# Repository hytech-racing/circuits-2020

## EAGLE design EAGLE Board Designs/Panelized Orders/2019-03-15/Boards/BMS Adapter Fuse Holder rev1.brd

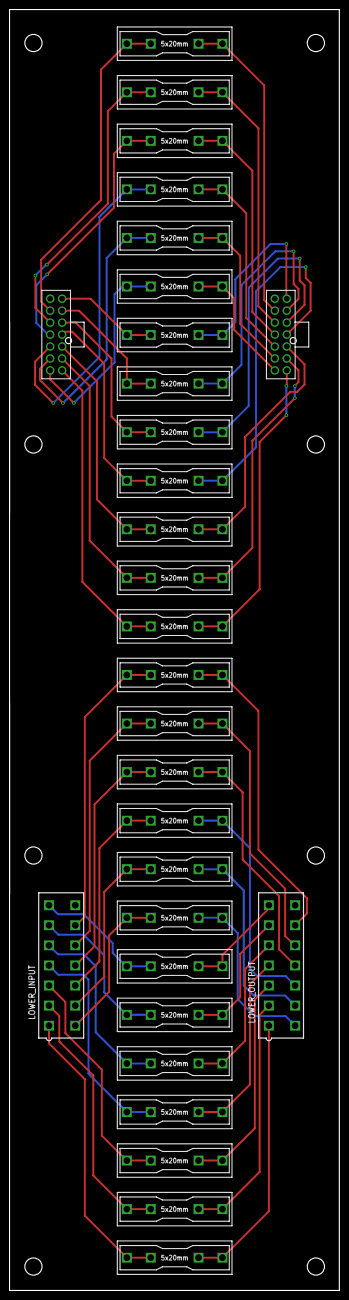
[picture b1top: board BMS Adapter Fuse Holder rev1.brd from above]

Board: 2 copper layers, 69.0 x 268.0 mm, 30 parts (0 on the bottom side), 52 nets.

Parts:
LOWER_INPUT: CONNECTOR-14; MINIFIT_5566-14
LOWER_OUTPUT: CONNECTOR-14; MINIFIT_5566-14
U$1, U$2, U$3, U$4, U$5, U$6, U$7, U$8, U$9, U$10, U$11, U$12, U$13, U$14, U$15, U$16, U$17, U$18, U$19, U$20, U$21, U$22, U$23, U$24, U$25, U$26: 1A; 0751.0110
UPPER_INPUT: CONNECTOR-14NANO-FIT_VERTICAL-14; NANO-FIT_VERTICAL-14
UPPER_OUTPUT: CONNECTOR-14NANO-FIT_VERTICAL-14; NANO-FIT_VERTICAL-14

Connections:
unnamed: LOWER_OUTPUT.1, U$1.L1, U$1.L2
unnamed: LOWER_OUTPUT.2, U$2.L1, U$2.L2
unnamed: LOWER_OUTPUT.3, U$3.L1, U$3.L2
unnamed: LOWER_OUTPUT.4, U$4.L1, U$4.L2
unnamed: LOWER_OUTPUT.5, U$5.L1, U$5.L2
unnamed: LOWER_OUTPUT.6, U$6.L1, U$6.L2
unnamed: LOWER_OUTPUT.7, U$7.L1, U$7.L2
unnamed: LOWER_OUTPUT.8, U$8.L1, U$8.L2
unnamed: LOWER_OUTPUT.9, U$9.L1, U$9.L2
unnamed: LOWER_OUTPUT.10, U$10.L1, U$10.L2
unnamed: LOWER_OUTPUT.11, U$11.L1, U$11.L2
unnamed: LOWER_OUTPUT.12, U$12.L1, U$12.L2
unnamed: LOWER_OUTPUT.13, U$13.L1, U$13.L2
unnamed: U$14.L1, U$14.L2, UPPER_OUTPUT.P$1
unnamed: U$15.L1, U$15.L2, UPPER_OUTPUT.P$2
unnamed: U$16.L1, U$16.L2, UPPER_OUTPUT.P$3
unnamed: U$17.L1, U$17.L2, UPPER_OUTPUT.P$4
unnamed: U$18.L1, U$18.L2, UPPER_OUTPUT.P$5
unnamed: U$19.L1, U$19.L2, UPPER_OUTPUT.P$6
unnamed: U$20.L1, U$20.L2, UPPER_OUTPUT.P$7
unnamed: U$21.L1, U$21.L2, UPPER_OUTPUT.P$8
unnamed: U$22.L1, U$22.L2, UPPER_OUTPUT.P$9
unnamed: U$23.L1, U$23.L2, UPPER_OUTPUT.P$10
unnamed: U$24.L1, U$24.L2, UPPER_OUTPUT.P$11
unnamed: U$25.L1, U$25.L2, UPPER_OUTPUT.P$12
unnamed: U$26.L1, U$26.L2, UPPER_OUTPUT.P$13
unnamed: LOWER_INPUT.1, U$1.R1, U$1.R2
unnamed: LOWER_INPUT.2, U$2.R1, U$2.R2
unnamed: LOWER_INPUT.3, U$3.R1, U$3.R2
unnamed: LOWER_INPUT.4, U$4.R1, U$4.R2
unnamed: LOWER_INPUT.5, U$5.R1, U$5.R2
unnamed: LOWER_INPUT.6, U$6.R1, U$6.R2
unnamed: LOWER_INPUT.7, U$7.R1, U$7.R2
unnamed: LOWER_INPUT.8, U$8.R1, U$8.R2
unnamed: LOWER_INPUT.9, U$9.R1, U$9.R2
unnamed: LOWER_INPUT.10, U$10.R1, U$10.R2
unnamed: LOWER_INPUT.11, U$11.R1, U$11.R2
unnamed: LOWER_INPUT.12, U$12.R1, U$12.R2
unnamed: LOWER_INPUT.13, U$13.R1, U$13.R2
unnamed: U$14.R1, U$14.R2, UPPER_INPUT.P$1
unnamed: U$15.R1, U$15.R2, UPPER_INPUT.P$2
unnamed: U$16.R1, U$16.R2, UPPER_INPUT.P$3
unnamed: U$17.R1, U$17.R2, UPPER_INPUT.P$4
unnamed: U$18.R1, U$18.R2, UPPER_INPUT.P$5
unnamed: U$19.R1, U$19.R2, UPPER_INPUT.P$6
unnamed: U$20.R1, U$20.R2, UPPER_INPUT.P$7
unnamed: U$21.R1, U$21.R2, UPPER_INPUT.P$8
unnamed: U$22.R1, U$22.R2, UPPER_INPUT.P$9
unnamed: U$23.R1, U$23.R2, UPPER_INPUT.P$10
unnamed: U$24.R1, U$24.R2, UPPER_INPUT.P$11
unnamed: U$25.R1, U$25.R2, UPPER_INPUT.P$12
unnamed: U$26.R1, U$26.R2, UPPER_INPUT.P$13

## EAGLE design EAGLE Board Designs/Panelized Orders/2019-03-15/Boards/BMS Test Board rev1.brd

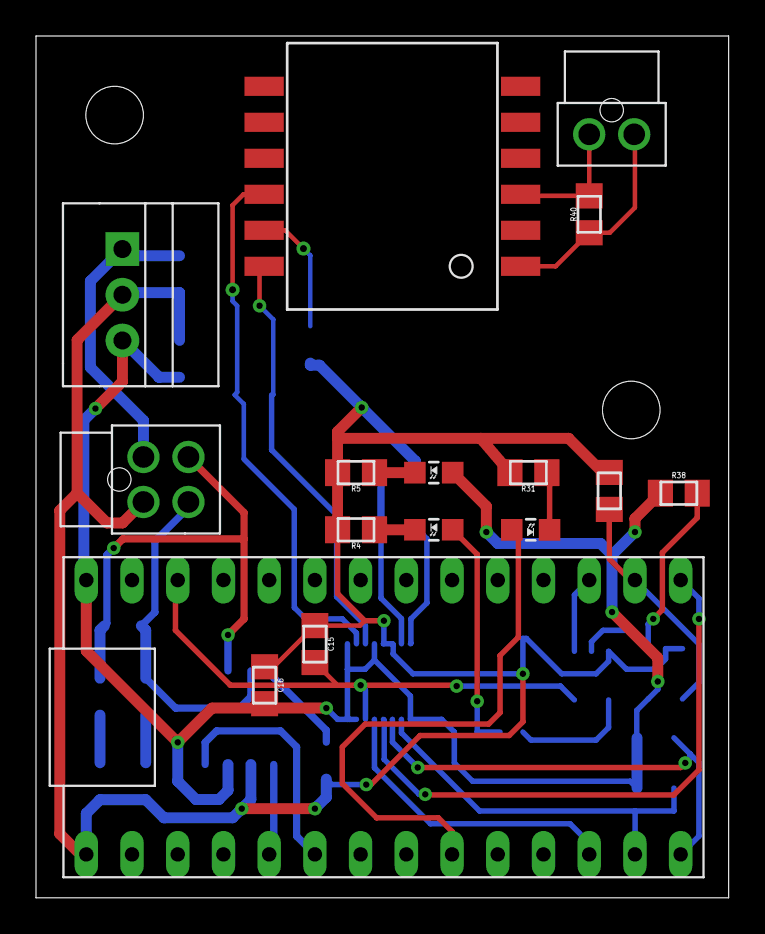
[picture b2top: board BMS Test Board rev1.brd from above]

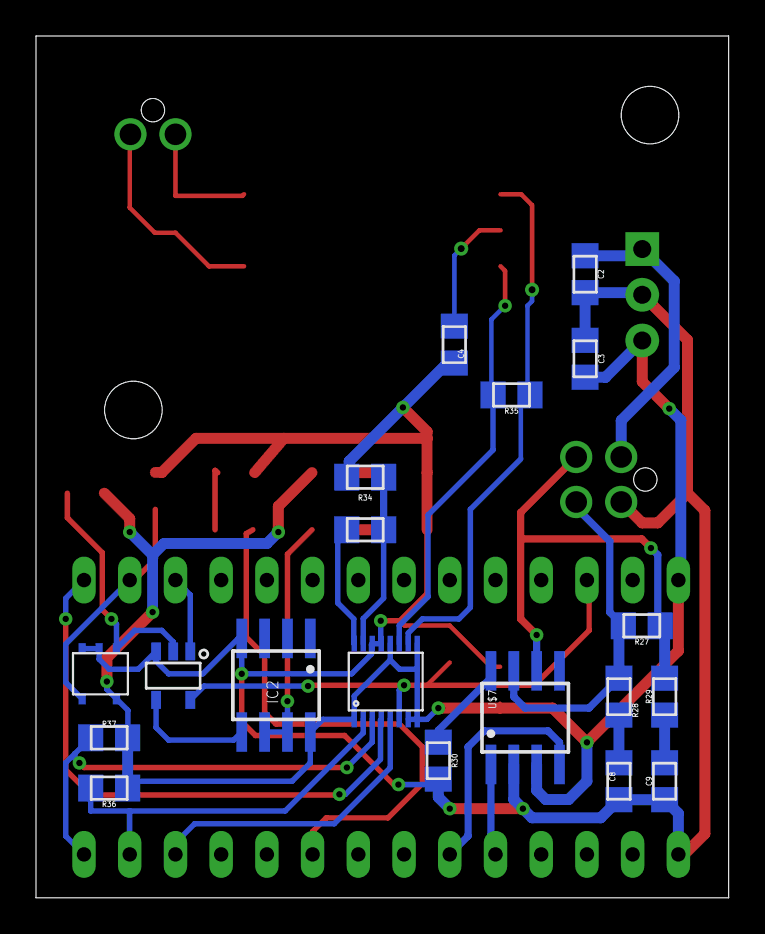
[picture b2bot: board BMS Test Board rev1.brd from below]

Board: 2 copper layers, 38.5 x 47.9 mm, 35 parts (19 on the bottom side), 31 nets.

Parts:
BMS-OK: GREEN; LED-805
C2, C3: 10uF; 0805
C4: 27pF; 0805
C8, C9: 560pF; 0805
C15, C16: 0.1uF; 0805
IC1: OKI-78SR-5; OKI-78SR
IC2: NE5532SOIC; SOIC-08
ISO_SPI: ISO_SPI; NANO-FIT_VERTICAL-2
ON-LED: PURPLE; LED-805
POWER: POWER; NANO-FIT_VERTICAL-4
R4: 820; 0805
R5: 270; 0805
R27, R35: 120; 0805
R28, R29, R40: 100; 0805
R30, R33, R34: 1k; 0805
R31, R38: 430; 0805
R36, R37: 2k; 0805
R42: 10k; 0805
TEENSY: BLUE; LED-805
U$2: HM2102NLT
U$3: SN74LVC1G08; SOT-23-5
U$7: MCP2551; SOIC-08
U$8: LTC6820; MSOP-16
U$9: TEENSY_3.2_SIMPLE
U$10: STWD100; SOT23-5

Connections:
+3V3: C15.2, U$3.5, U$8.6, U$9.3.3V
+5V: C3.1, C16.2, IC1.3, IC2.8, ON-LED.A, R36.1, R37.1, R38.1, U$7.3, U$8.1, U$8.7, U$8.8, U$8.9, U$8.12, U$9.VIN, U$10.VCC
+12V: C2.1, IC1.1, POWER.P$1
BMS_OK: IC2.5, U$3.4
CANH: POWER.P$4, R27.2, R28.2, U$7.7
CANL: POWER.P$3, R27.1, R29.2, U$7.6
CS_LTC6820: U$8.5, U$9.D10(TX2)
GND: C2.2, C3.2, C4.2, C8.1, C9.1, C15.1, C16.1, IC1.2, IC2.4, POWER.P$2, R4.2, R5.2, R30.1, R31.2, R34.2, R42.2, U$3.3, U$7.2, U$8.13, U$8.14, U$9.GND, U$10.EN, U$10.GND
IM: R35.1, U$2.P$10, U$8.10
IP: R35.2, U$2.P$12, U$8.11
ISOSPI-M: ISO_SPI.P$2, R40.2, U$2.P$3
ISOSPI-P: ISO_SPI.P$1, R40.1, U$2.P$1
MISO: R37.2, U$8.3, U$9.D12
MOSI_TEENSY: R36.2, U$8.2, U$9.D11
unnamed: ON-LED.C, R5.1
unnamed: U$7.1, U$9.D3(CANTX)
unnamed: R30.2, U$7.8
unnamed: C8.2, R28.1
unnamed: C9.2, R29.1
unnamed: R31.1, TEENSY.C
unnamed: R33.1, U$8.16
unnamed: R33.2, R34.1, U$8.15
unnamed: C4.1, U$2.P$11
unnamed: U$7.4, U$9.D4(CANRX)
unnamed: TEENSY.A, U$9.D7(RX3)
unnamed: R38.2, U$3.2, U$10.WDO
unnamed: U$3.1, U$9.A1
unnamed: BMS-OK.A, IC2.6, IC2.7
unnamed: BMS-OK.C, R4.1
unnamed: R42.1, U$9.A0, U$10.WDI
SCK_TEENSY: U$8.4, U$9.D13

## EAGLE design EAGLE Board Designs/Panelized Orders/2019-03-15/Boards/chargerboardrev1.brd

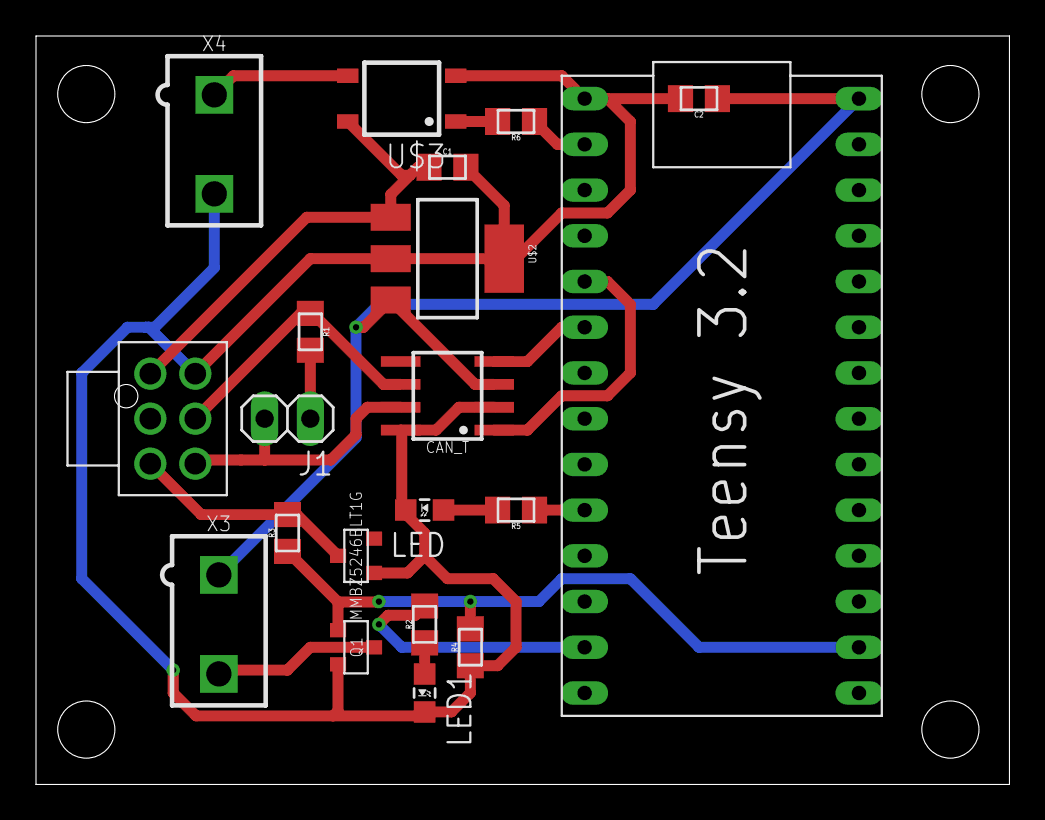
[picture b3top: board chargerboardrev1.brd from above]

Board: 2 copper layers, 54.1 x 41.6 mm, 20 parts (0 on the bottom side), 18 nets.

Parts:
C1, C2: 0.22uF; 0805
CAN_T: MCP2551; SOIC-08
J1: JUMPER.1; 1X02
LED, LED1: LED-805
MMBZ5246BLT1G: DIODE_ZENER; SOT23
Q1: SOT23
R1: 120; 0805
R2, R5: 1.2k; 0805
R3: 20k; 0805
R4: 10k; 0805
R6: 330; 0805
U$1: TEENSY_3.2_SIMPLE
U$2: SOT223
U$3: CPC1002N; SOP04
X1: CONNECTOR-6NANO-FIT_VERTICAL-6; NANO-FIT_VERTICAL-6
X3, X4: CONNECTOR-2; MINIFIT_5566-2

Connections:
5V: C2.1, CAN_T.3, U$1.VIN, U$2.3, X3.1
12V: C1.1, U$2.1, U$3.4, X1.P$1
CANH: CAN_T.7, J1.2, X1.P$6
CANL: CAN_T.6, R1.1, X1.P$5
CANRX: CAN_T.4, U$1.D4(CANRX)
CANTX: CAN_T.1, U$1.D3(CANTX)
CHARGE_ENABLE: MMBZ5246BLT1G.3, R3.2, X1.P$3
CHRG_C: R6.1, U$1.D0(RX1)
GND: C1.2, C2.2, CAN_T.2, CAN_T.8, LED.C, LED1.C, MMBZ5246BLT1G.1, Q1.2, R4.1, U$1.GND, U$2.2, U$2.4, U$3.2, X1.P$4, X4.2
unnamed: Q1.3, X3.2
unnamed: R2.2, U$1.D11
unnamed: R5.1, U$1.D8(TX3)
unnamed: LED1.A, R2.1
unnamed: J1.1, R1.2
unnamed: LED.A, R5.2
unnamed: U$3.3, X4.1
unnamed: R6.2, U$3.1
SIGNAL_SAFE: Q1.1, R3.1, R4.2, U$1.A0

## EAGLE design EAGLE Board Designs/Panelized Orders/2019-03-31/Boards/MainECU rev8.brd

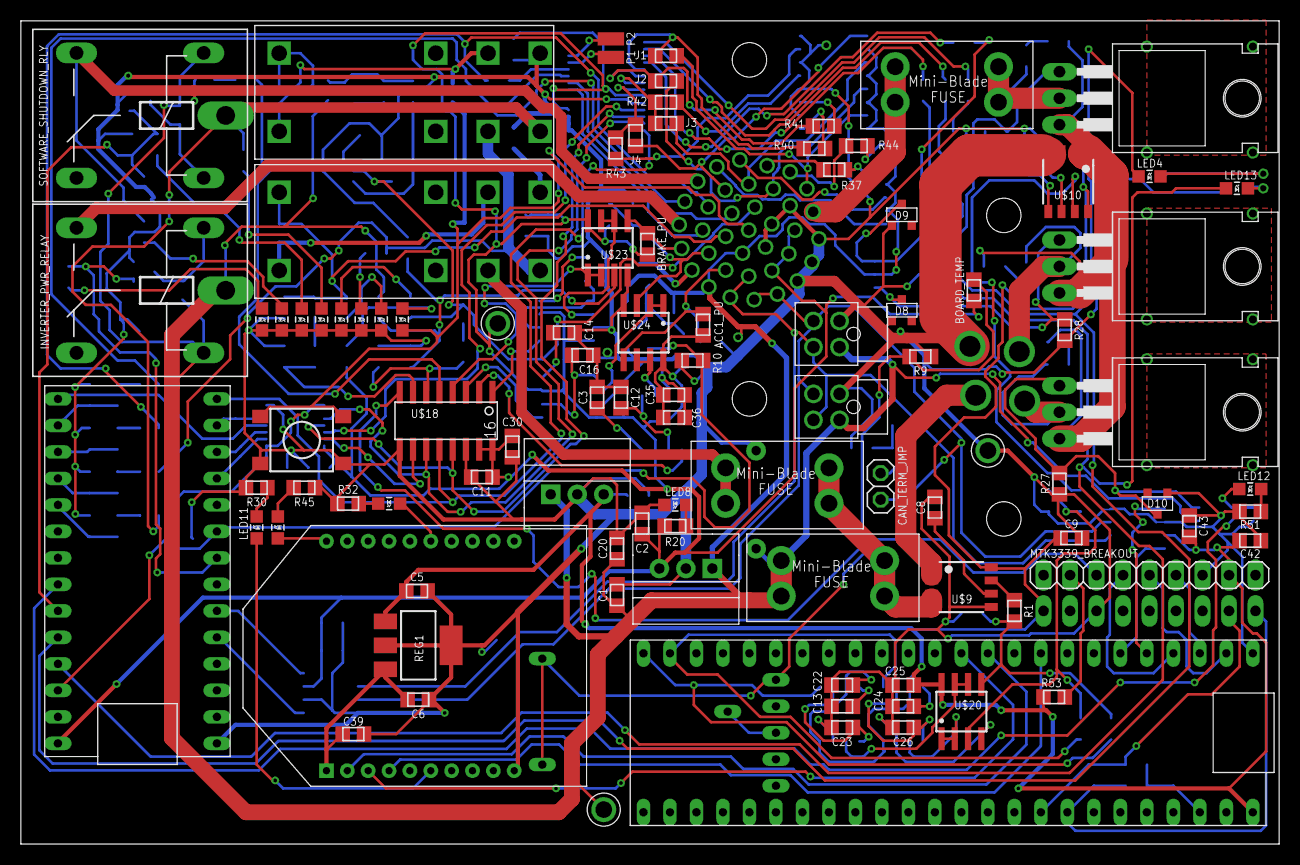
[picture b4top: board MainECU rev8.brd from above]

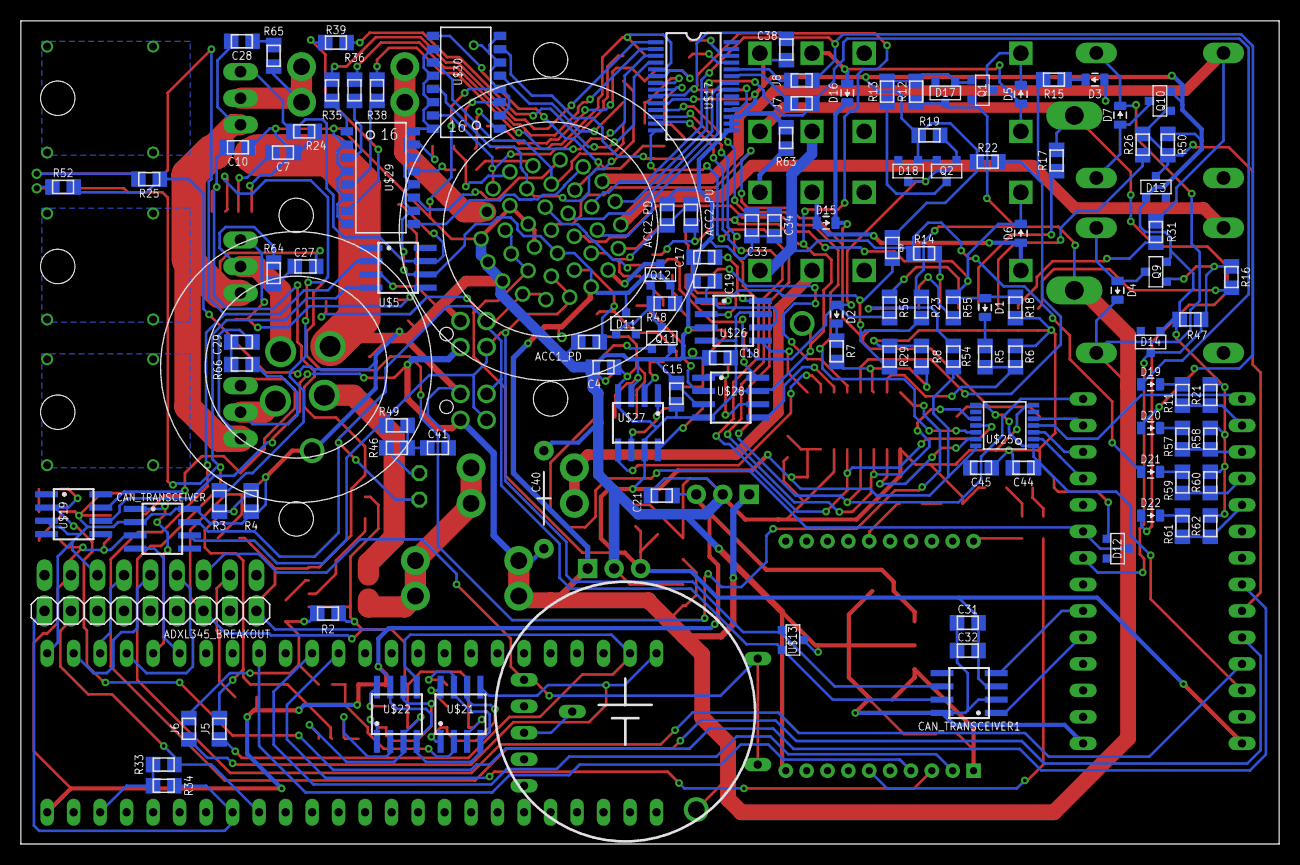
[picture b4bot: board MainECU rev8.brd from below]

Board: 4 copper layers, 120.6 x 78.9 mm, 218 parts (120 on the bottom side), 170 nets.

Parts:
5ABOARDFUSE, 5AFUSE, 5ASHUTDOWNFUSE: MINI-BLADE_FUSE_HOLDER
ACC1_PD, ACC1_PU, ACC2_PD, ACC2_PU: 10k; 0805
ADXL345_BREAKOUT: 1X09
BMS_SHUTDOWN_RLY: RT424012; RELAY_DPDT
BOARD_TEMP: THERMISTOR_NCP210805; 0805
BRAKE_PU: 10k; 0805
C1, C2, C20, C21: 10uF; 0805
C3, C7, C8, C14, C17: 47nF; 0805
C4, C12, C15, C16, C18, C19, C22, C23, C25, C26, C32, C34, C36, C43, C44, C45: .1uF; 0805
C5, C6, C11, C31, C33, C35, C37, C42: 1uF; 0805
C9, C10, C30, C38, C39: 0.1uF; 0805
C13, C24: 470pF; 0805
C27, C28, C29: 0805
C40: 470uF; CAP-PTH-LARGE
C41: 4.7nF; 0805
CAN_TERM_JMP: M02_SLIM; 1X02_SLIM
CAN_TRANSCEIVER, CAN_TRANSCEIVER1: MCP2551; SOIC-08
D1, D2, D3, D4, D5, D6, D7, D15, D16, D19, D20, D21, D22: TS4148 RYG; 0805_D
D8, D9, D10, D11, D12, D13, D14, D17, D18: MMBZ5246BLT1G; SOT23
IMD_SHUTDOWN_RLY: RT424009; RELAY_DPDT
INVERTER_PWR_RELAY: G5LE; ZF112
J1, J2, J3, J4, J5, J6, J7, J8: JUMPER; 0805
LED1: White; LED-805
LED3, LED7, LED11: Green; LED-805
LED4, LED6, LED10, LED12, LED13, LED17, LED18: Red; LED-805
LED5, LED9: Yellow; LED-805
LED8: Purple; LED-805
LED14: Blue; LED-805
MTK3339_BREAKOUT: 1X09
P1, P2: SOLDER_PAD; SOLDER_PAD_XSMALL
Q1, Q12: P-CHANNEL_MOSFET_DMP3099L-7; SOT23
Q2, Q9, Q10, Q11: SOT23
R1, R3: 1K; 0805
R2, R4: 2K; 0805
R5, R7, R11, R15, R23, R57, R59, R61: 43k; 0805
R6, R8, R21, R22, R29, R58, R60, R62: 12k; 0805
R9, R10, R12, R19, R24, R27, R28, R47, R48, R50, R53: 10k; 0805
R13: 1k; 0805
R14, R18, R55: 2k; 0805
R16, R25, R32, R51, R52: 1.2k; 0805
R17: 20k; 0805
R20: 270; 0805
R26: 1.2K; 0805
R30, R56: 33; 0805
R31: 6.8k; 0805
R33, R34: 4.7k; 0805
R35, R36, R38, R39, R40, R41, R42, R43: 150; 0805
R37, R44, R45: 0; 0805
R46, R49: 60; 0805
R54: 5.1k; 0805
R63: 20; 0805
R64, R65, R66: 0805
REG, REG3: 5V; OKI-78SR
REG1: LM3940; SOT223
S1: TACTILE_SWITCH_SMD_6.2MM_TALL
SOFTWARE_SHUTDOWN_RLY: G5LE; ZF112
U$1: TEENSY_3.2_SIMPLE
U$2: TEENSY_3.5_EXT
U$3: XBEE
U$4, U$6, U$7: N-CHANNEL_MOSFET_IRF1324PBF; TO-220-H-HOLE
U$5, U$19: MC34152; SOIC-08
U$8, U$11, U$12: TEST_POINT
U$9, U$10: ACS715_CURRENT_SENSOR; SOP8
U$13: CDSOT23-T24CAN-Q; SOT23
U$16: CR-2450/G1AN
U$17: MCP23S17SSOP28; SSOP28
U$18: MCP3208SOIC; SOIC-16
U$20, U$23, U$24: MCP6002SOIC; SOIC-08
U$21, U$22, U$26, U$27, U$28: SOIC-08
U$25: TXB0104TSSOP; TSSOP-14
U$29, U$30: TLP291-4; 11-11F1
X1: CONNECTOR-37; AUTOSPORT_14-35
X2: CONNECTOR-4AUTOSPORT; AUTOSPORT_12-04
X3, X4: CONNECTOR-4NANO-FIT-VERTICAL-4; NANO-FIT_VERTICAL-4

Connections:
3.3V: R33.2, R34.2, U$2.3.3V
3.3V_MAIN_TEENSY: C44.1, U$1.3.3V, U$25.1, U$25.8
12VIN: U$9.1, U$9.2, X2.P$1
12VSUPPLY_DIV: C37.2, R23.2, R29.1, U$23.3
12VSUPPLY_READ: U$18.4, U$23.1, U$23.2
12VUNFUSED: 5ABOARDFUSE.L1, 5ABOARDFUSE.L2, 5ASHUTDOWNFUSE.L1, 5ASHUTDOWNFUSE.L2, U$9.3, U$9.4
+5V: ACC1_PU.2, ACC2_PU.2, BOARD_TEMP.1, BRAKE_PU.2, C2.2, C4.1, C11.2, C15.1, C18.1, C30.2, C31.2, C32.2, C33.2, C34.2, C35.1, C36.1, C38.1, C45.1, CAN_TRANSCEIVER1.3, R20.1, R54.1, REG.3, U$1.VIN, U$11.P$1, U$17.9, U$17.18, U$18.15, U$18.16, U$23.8, U$24.8, U$25.14, U$26.4, U$26.7, U$27.4, U$27.7, U$28.4, U$28.7, X1.P$27, X1.P$28, X1.P$29
+12V: 5ABOARDFUSE.R1, 5ABOARDFUSE.R2, C1.2, C20.2, C40.1, D4.C, D7.C, D11.3, D17.3, INVERTER_PWR_RELAY.1, INVERTER_PWR_RELAY.P, Q1.2, Q12.2, R12.1, R23.1, R48.1, REG.1, REG3.1, SOFTWARE_SHUTDOWN_RLY.2, U$5.6, U$8.P$1, U$19.6, U$29.10, U$29.12, U$29.14, U$29.16, U$30.10, U$30.12, U$30.14, U$30.16, X1.P$10, X1.P$34, X3.P$1, X4.P$1
BMS_OK: D2.A, D18.3, Q2.1, R19.1, R56.1, X1.P$31
BMS_OK_READ: R7.2, R8.1, U$18.6
BMS_OK_SW: BMS_SHUTDOWN_RLY.COIL+, D5.C, Q1.3
BMS_PWR_STEP: BMS_SHUTDOWN_RLY.3, BMS_SHUTDOWN_RLY.COIL-, D5.A, D16.A
BRAKE_LIGHT: Q12.3, X1.P$9
BRAKE_LIGHT_CTRL: D12.3, Q11.1, R10.2, U$1.D7(RX3)
CANH: CAN_TERM_JMP.1, CAN_TRANSCEIVER.7, CAN_TRANSCEIVER1.7, U$13.2, X1.P$12, X1.P$13, X3.P$4, X4.P$4
CANL: CAN_TRANSCEIVER.6, CAN_TRANSCEIVER1.6, R49.1, U$13.1, X1.P$11, X1.P$26, X3.P$3, X4.P$3
COOLINGSENSE: J5.2, R3.2, R4.2, U$20.3
COOLINGSENSE_FILT: J5.1, U$2.A12, U$22.5
CS1_5V: U$18.10, U$25.13
CS1_TEENSY: U$1.D9(RX2), U$25.2
CS2_5V: U$17.11, U$25.12
CS2_TEENSY: U$1.D10(TX2), U$25.3
CURRENTSENSE2: C27.2, C28.2, C29.2, U$4.3, U$6.3, U$7.3, U$10.1, U$10.2
DASH11_READ: R11.2, R21.1, U$1.A0
DASH12_READ: R57.2, R58.1, U$1.A1
DASH_1_EXTERN: R44.2, X1.P$1
DASH_1_INTER: R35.1, U$17.1
DASH_2_EXTERN: R37.2, X1.P$2
DASH_2_INTER: R36.1, U$17.2
DASH_3_EXTERN: U$29.11, X1.P$3
DASH_3_INTER: R38.1, U$17.3
DASH_4_EXTERN: U$29.9, X1.P$4
DASH_4_INTER: R39.1, U$17.4
DASH_5_EXTERN: J1.1, U$30.15, X1.P$18
DASH_5_INTER: J1.2, R40.1, U$17.5
DASH_6_EXTERN: J2.1, U$30.13, X1.P$19
DASH_6_INTER: J2.2, R41.1, U$17.6
DASH_7_EXTERN: J3.1, U$30.11, X1.P$20
DASH_7_INTER: J3.2, R42.1, U$17.7
DASH_8_EXTERN: J4.1, U$30.9, X1.P$21
DASH_8_INTER: J4.2, R43.1, U$17.8
DASH_9_EXTERN: U$17.21, X1.P$23
DASH_10_EXTERN: U$17.22, X1.P$32
DASH_11_EXTERN: D19.A, J7.1, X1.P$6
DASH_11_INTER: J7.2, U$17.23
DASH_12_EXTERN: D20.A, J8.1, X1.P$22
DASH_12_INTER: J8.2, U$17.24
ECUSENSE: J6.2, R1.2, R2.2, U$20.5
ECUSENSE_FILT: J6.1, U$2.A13, U$21.5
FAN1-: 5AFUSE.R1, 5AFUSE.R2, R65.1, U$7.2
FAN1CONTROL: LED4.A, U$1.A8, U$5.2
FAN1DRIVE: D9.3, R24.2, U$5.7, U$7.1
FAN2-: R64.1, U$4.2, X2.P$3
FAN2CONTROL: LED13.A, U$1.A9, U$5.4
FAN2DRIVE: D8.3, R28.2, U$4.1, U$5.5
GND: ACC1_PD.2, ACC2_PD.2, ADXL345_BREAKOUT.3, BMS_SHUTDOWN_RLY.4, C1.1, C2.1, C3.2, C4.2, C5.2, C6.1, C7.2, C8.2, C9.2, C10.2, C11.1, C12.1, C13.2, C14.2, C15.2, C16.1, C17.2, C18.2, C19.1, C20.1, C21.1, C22.2, C23.1, C24.2, C25.2, C26.1, C30.1, C31.1, C32.1, C33.1, C34.1, C35.2, C36.2, C37.1, C38.2, C39.2, C40.2, C41.2, C42.1, C43.1, C44.2, C45.2, CAN_TRANSCEIVER.2, CAN_TRANSCEIVER.8, CAN_TRANSCEIVER1.2, CAN_TRANSCEIVER1.8, D8.1, D9.1, D10.1, D12.1, D13.1, D14.1, D18.1, LED3.C, LED5.C, LED6.C, LED7.C, LED8.C, LED9.C, LED17.C, LED18.C, MTK3339_BREAKOUT.7, Q2.2, Q9.2, Q10.2, Q11.2, R2.1, R4.1, R6.2, R8.2, R9.1, R10.1, R18.2, R19.2, R21.2, R22.2, R24.1, R25.2, R27.1, R28.1, R29.2, R30.1, R32.1, R45.1, R47.2, R50.2, R51.2, R52.2, R58.2, R60.2, R62.2, R63.2, REG.2, REG1.2, REG1.4, REG3.2, S1.B1, S1.B2, U$1.GND, U$2.GND, U$3.10, U$5.3, U$9.5, U$10.3, U$10.4, U$10.5, U$12.P$1, U$13.3, U$17.10, U$17.15, U$17.16, U$17.17, U$18.9, U$18.14, U$19.3, U$20.4, U$21.3, U$22.3, U$23.4, U$24.4, U$25.7, U$26.3, U$27.3, U$28.3, U$29.2, U$29.4, U$29.6, U$29.8, U$30.2, U$30.4, U$30.6, U$30.8, X1.P$14, X1.P$15, X1.P$16, X1.P$30, X1.P$35, X1.P$36, X2.P$4, X3.P$2, X4.P$2
IMD_PWR_STEP: D6.A, D15.A, IMD_SHUTDOWN_RLY.3, IMD_SHUTDOWN_RLY.COIL-
INVERTER_CTRL: D14.3, Q9.1, R16.1, R47.1, U$1.D6
INVERTER_SUPPLY: INVERTER_PWR_RELAY.S, X1.P$7
LATCH_EXT_BUTTON: D15.C, D16.C, LED1.C, S1.A1, S1.A2, X1.P$37
MISO_TEENSY: U$1.D12, U$17.14, U$18.12
MOSI_5V: U$17.13, U$18.11, U$25.10
MOSI_TEENSY: U$1.D11, U$25.5
MTK3339_DIN: MTK3339_BREAKOUT.6, U$2.D1(TX1)
MTK3339_DOUT: MTK3339_BREAKOUT.5, U$2.D0(RX1)
MTK3339_FIX: MTK3339_BREAKOUT.4, U$2.D2
unnamed: 5AFUSE.L1, 5AFUSE.L2, X1.P$17
unnamed: LED1.A, R54.2
unnamed: R1.1, U$9.7
unnamed: C12.2, U$27.1, U$27.6
unnamed: D20.C, R57.1
unnamed: R3.1, U$10.7
unnamed: MTK3339_BREAKOUT.2, R53.2
unnamed: C8.1, U$9.6
unnamed: LED3.A, R56.2
unnamed: D1.C, R5.1
unnamed: D2.C, R7.1
unnamed: D17.1, Q1.1, R12.2, R13.2
unnamed: CAN_TRANSCEIVER.4, U$2.D4(CANRX)
unnamed: CAN_TRANSCEIVER.1, U$2.D3(CANTX)
unnamed: CAN_TRANSCEIVER1.4, U$1.D4(CANRX)
unnamed: Q2.3, R13.1
unnamed: CAN_TERM_JMP.2, R46.2
unnamed: D19.C, R11.1
unnamed: LED5.A, R14.2
unnamed: U$20.1, U$20.2, U$22.2
unnamed: C3.1, U$27.8
unnamed: CAN_TRANSCEIVER1.1, U$1.D3(CANTX)
unnamed: U$24.1, U$24.2, U$28.2
unnamed: U$24.6, U$24.7, U$27.2
unnamed: U$23.6, U$23.7, U$26.2
unnamed: LED9.A, R55.2
unnamed: D7.A, Q10.3, SOFTWARE_SHUTDOWN_RLY.1
unnamed: LED6.A, R16.2
unnamed: LED8.A, R20.2
unnamed: R36.2, U$29.3
unnamed: D21.C, R59.1
unnamed: LED7.A, R17.2
unnamed: D3.C, R15.1
unnamed: D22.C, R61.1
unnamed: LED14.C, R45.2
unnamed: C16.2, U$28.1, U$28.6
unnamed: C19.2, U$26.1, U$26.6
unnamed: C14.1, U$28.8
unnamed: U$20.6, U$20.7, U$21.2
unnamed: LED18.A, R31.2
unnamed: C17.1, U$26.8
unnamed: R37.1, U$29.13
unnamed: C23.2, U$21.1, U$21.6
unnamed: C13.1, U$21.8
unnamed: LED11.C, R30.2
unnamed: LED17.A, R26.2
unnamed: LED11.A, U$3.6
unnamed: C7.1, U$10.6
unnamed: LED10.A, U$3.15
unnamed: LED10.C, R32.2
unnamed: R35.2, U$29.1
unnamed: R38.2, U$29.5
unnamed: R39.2, U$29.7
unnamed: R40.2, U$30.1
unnamed: R41.2, U$30.3
unnamed: R42.2, U$30.5
unnamed: R43.2, U$30.7
unnamed: D11.1, Q11.3, Q12.1, R48.2
unnamed: R44.1, U$29.15
unnamed: IMD_SHUTDOWN_RLY.4, R63.1
unnamed: U$2.GND_2, U$16.-
unnamed: C41.1, R46.1, R49.2
unnamed: LED14.A, U$3.20
unnamed: C27.1, R64.2
unnamed: D4.A, INVERTER_PWR_RELAY.2, Q9.3
unnamed: C26.2, U$22.1, U$22.6
unnamed: C24.1, U$22.8
unnamed: LED4.C, R25.1
unnamed: LED12.C, R51.1
unnamed: LED13.C, R52.1
unnamed: P1.P$1, U$17.25
unnamed: P2.P$1, U$17.26
unnamed: C28.1, R65.2
unnamed: C29.1, R66.2
OKHS: D1.A, D6.C, IMD_SHUTDOWN_RLY.COIL+, R18.1, R55.1, X1.P$33
OKHS_READ: R5.2, R6.1, U$18.7
PUMP1-: R66.1, U$6.2, X2.P$2
PUMPCONTROL: LED12.A, U$1.A6, U$19.2
PUMPDRIVE: D10.3, R27.2, U$6.1, U$19.7
READ_ACCEL1: U$18.2, U$27.5
READ_ACCEL2: U$18.3, U$28.5
READ_BRAKE: U$18.1, U$26.5
SCK_5V: U$17.12, U$18.13, U$25.11
SCK_TEENSY: U$1.D13, U$25.4
SCL: ADXL345_BREAKOUT.9, R34.1, U$2.A5
SDA: ADXL345_BREAKOUT.8, R33.1, U$2.A4
SHUTDOWN_A: 5ASHUTDOWNFUSE.R1, 5ASHUTDOWNFUSE.R2, IMD_SHUTDOWN_RLY.6
SHUTDOWN_B: BMS_SHUTDOWN_RLY.6, D21.A, IMD_SHUTDOWN_RLY.5, R14.1
SHUTDOWN_B_READ: R59.2, R60.1, U$1.A2
SHUTDOWN_C: BMS_SHUTDOWN_RLY.5, D22.A, R17.1, SOFTWARE_SHUTDOWN_RLY.P
SHUTDOWN_C_READ: R61.2, R62.1, U$1.A3
SHUTDOWN_D: D3.A, R31.1, SOFTWARE_SHUTDOWN_RLY.S, X1.P$5
SHUTDOWN_OUT_READ: R15.2, R22.1, U$18.5
SIGNAL_ACCEL1: ACC1_PD.1, ACC1_PU.1, U$24.5, X1.P$25
SIGNAL_ACCEL2: ACC2_PD.1, ACC2_PU.1, U$24.3, X1.P$24
SIGNAL_BRAKE: BRAKE_PU.1, U$23.5, X1.P$8
SOFTWARE_SHUTDOWN: D13.3, Q10.1, R26.1, R50.1, U$1.A7
TELEMETRY5V: ADXL345_BREAKOUT.1, C5.1, C9.1, C10.1, C21.2, C22.1, C25.1, C42.2, C43.2, CAN_TRANSCEIVER.3, MTK3339_BREAKOUT.8, R53.1, REG1.1, REG3.3, U$2.VIN, U$9.8, U$10.8, U$20.8, U$21.4, U$21.7, U$22.4, U$22.7
TEMPSENSE: BOARD_TEMP.2, R9.2, U$18.8
VBAT_RTC: MTK3339_BREAKOUT.3, U$2.VBAT, U$16.+_0, U$16.+_1
VCC: C6.2, C39.1, REG1.3, U$3.1
XB8: U$2.D7(RX3), U$3.4
XBDI: U$2.D10(TX2), U$3.3
XBDO: U$2.D9(RX2), U$3.2
